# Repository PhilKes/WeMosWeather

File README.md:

# WeMosWeather  
## 3D Printed Solar powered Weather station
## Station

* 3D Printed Case (PLA) (created with [Autodesk 123Design](https://autodesk-123d-design.en.lo4d.com/windows))
* [BME 280](https://de.aliexpress.com/item/32801639254.html?src=google&src=google&albch=shopping&acnt=494-037-6276&isdl=y&slnk=&plac=&mtctp=&albbt=Gploogle_7_shopping&aff_atform=google&aff_short_key=UneMJZVf&&albagn=888888&albcp=1705854617&albag=67310370915&trgt=743612850714&crea=de32801639254&netw=u&device=c&albpg=743612850714&albpd=de32801639254&gclid=EAIaIQobChMIqMSEpN7e6gIVkLt3Ch35YAZTEAQYASABEgLxBfD_BwE&gclsrc=aw.ds)
* [WeMos D1 Mini](https://docs.wemos.cc/en/latest/d1/d1_mini.html)
* Light Sensor
* 3.7V Lithium Ion Battery 18650

## Sketch
* Arduino .ino Sketch for WeMos D1 mini/ESP ([sketch_solar_weather_thingspeak](/sketch_solar_weather_thingspeak))
* Reads and Posts Sensor Data to Thingspeak in interval (every 5 min)
* Uses ESP.deepSleep to save most Power

#### Dependencies
* [ESPAsyncWebServer](https://github.com/me-no-dev/ESPAsyncWebServer)
* [ESPAsyncTCP](https://github.com/me-no-dev/ESPAsyncTCP)
* [ESP8266-FS-Uploader](https://randomnerdtutorials.com/install-esp8266-filesystem-uploader-arduino-ide/)

## Android App

* Fetches Data from Thingspeak Server
* Displays Data on UI Dashboard
* Shows History of all collected Data

### TODOs
* Home Screen Widget
* Weather Prediction based on Pressure values

#### Dependencies
* [HelloCharts](https://github.com/lecho/hellocharts-android)
* [Material Design](https://material.io/components)

## Thingspeak Api
* Create a free Account on Thingspeak
* Add a private Channel with Field 1 (Temperature), Field 2 (Pressure), Field 3 (Humidity)
* To allow the Android App and WeMos Sketch to post/read Data to/from Thingspeak add the following files:

/sketch/solar_weather_thingspeak/**api.h**:

    const char* api_key = <YOUR_THINGSPEAK_CHANNEL_API_KEY>;
    char ssid[] = <YOUR_WIFI>;
    char pass[] = <WIFI_PASSWORD>;

/android/app/src/main/res/values/**api.xml**:

    <?xml version="1.0" encoding="utf-8"?>
    <resources>
        <item name="THINGSPEAK_READ_KEY" type="string"><YOUR_THINGSPEAK_CHANNEL_READ_KEY></item>
        <item name="THINGSPEAK_CHANNEL" type="string"><YOUR_THINGSPEAK_CHANNEL_ID></item>
    </resources>

## Web Page
* Alternative [sketch_solar_weather_webasync](/sketch_solar_weather_webasync)
* Basic static HTML Page to View Station Data directly from the WeMos
* Bootstrap Design
* URL: http://<WEMOS_IP_ADRESS>

### Sources
* [Thingspeak](https://thingspeak.com/)
* [Instructables](https://www.instructables.com/id/Solar-Powered-WiFi-Weather-Station/)
* [Esp8266 Bootstrap Example](https://diyprojects.io/bootstrap-create-beautiful-web-interface-projects-esp8266/#.XxcEGJ4zaUk)

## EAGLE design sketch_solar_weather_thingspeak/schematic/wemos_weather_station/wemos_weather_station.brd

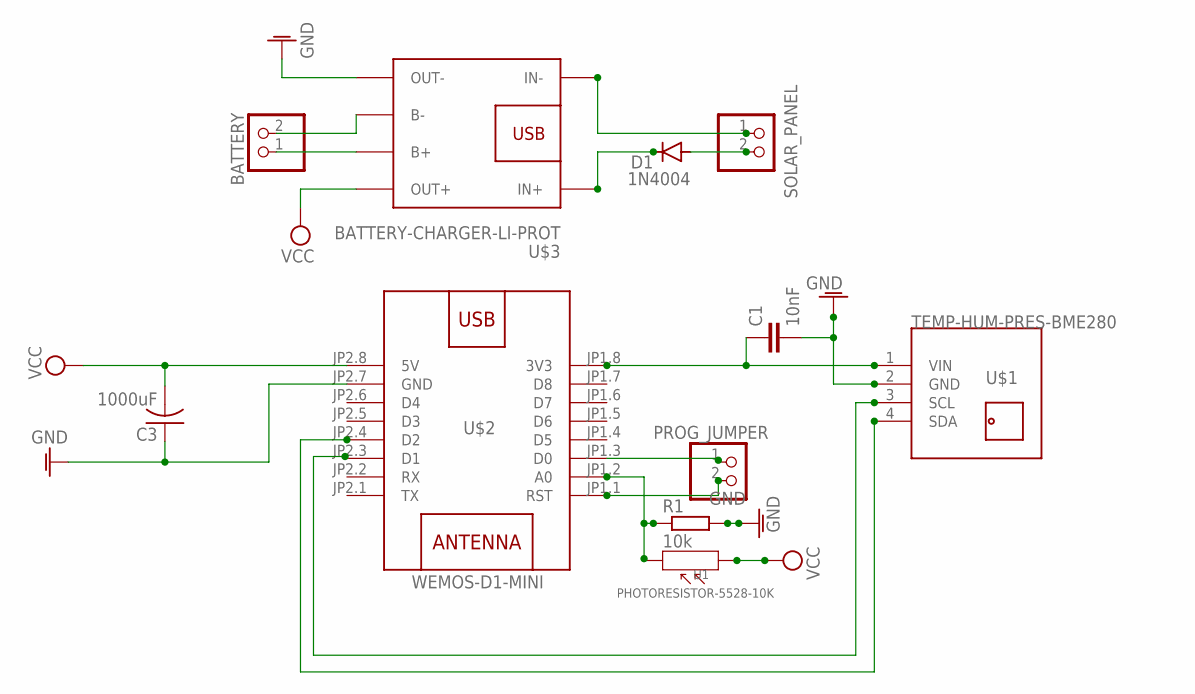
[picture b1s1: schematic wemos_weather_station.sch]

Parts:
BATTERY: PINHD-1X2; 1X02
C1: 10nF; C025-025X050
C3: 1000uF; C050-024X044
D1: 1N4004; DO41-10
PROG_JUMPER: PINHD-1X2; 1X02
R1: 10k; 0204/7
SOLAR_PANEL: PINHD-1X2; 1X02
U1: PHOTORESISTOR-5528-10K; SNR2-3.0
U$1: TEMP-HUM-PRES-BME280
U$2: WEMOS-D1-MINI
U$3: BATTERY-CHARGER-LI-PROT

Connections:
GND: C1.2, C3.1, R1.2, U$1.2 (GND), U$2.JP2.7 (GND), U$3.OUT-
unnamed: SOLAR_PANEL.1, U$3.IN-
unnamed: D1.C, U$3.IN+
unnamed: BATTERY.1, U$3.B+
unnamed: BATTERY.2, U$3.B-
unnamed: D1.A, SOLAR_PANEL.2
unnamed: PROG_JUMPER.1, U$2.JP1.3 (D0)
unnamed: C1.1, U$1.1 (VIN), U$2.JP1.8 (3V3)
unnamed: U$1.4 (SDA), U$2.JP2.4 (D2)
unnamed: U$1.3 (SCL), U$2.JP2.3 (D1)
unnamed: PROG_JUMPER.2, U$2.JP1.1 (RST)
unnamed: R1.1, U1.2, U$2.JP1.2 (A0)
VCC: C3.2, U1.1, U$2.JP2.8 (5V), U$3.OUT+

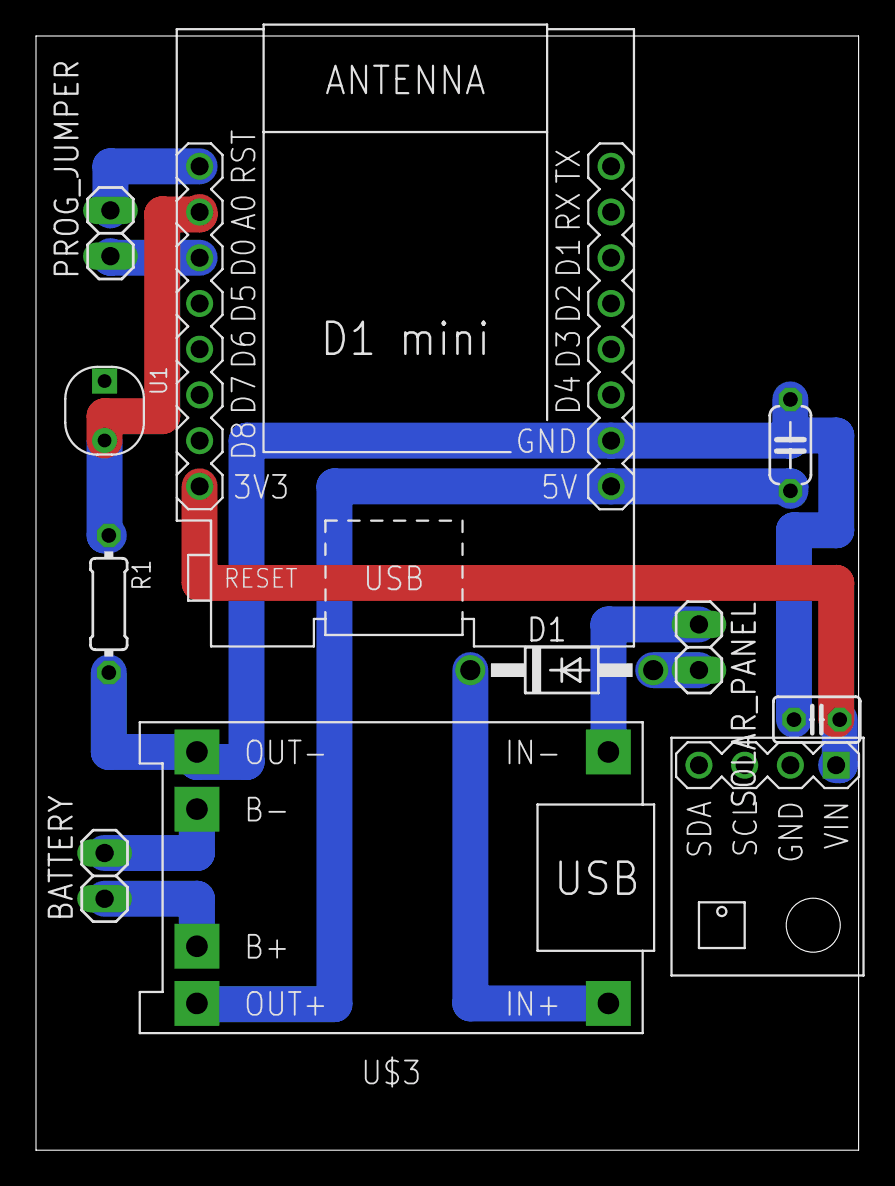
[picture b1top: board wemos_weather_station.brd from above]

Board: 2 copper layers, 45.7 x 61.9 mm, 11 parts (0 on the bottom side), 13 nets.

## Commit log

2020-07-21 initial web sketch with bootstrap
2020-07-21 webpage.html + .gitignore added
2020-07-23 Charts.js + NTPClient added
2020-07-23 AsyncWebServer with HTTP Endpoints + SPIFF Data Upload
2020-07-23 Placeholder in index.html + continous updates + Buffer for 24h, update every 5 min
2020-07-24 Android app added
2020-07-25 feat: Android App with Temperature + Humidity display + HTTP Updates
2020-07-25 assets: Logo added
2020-07-25 README.md updated
2020-07-25 assets/logo.png added
2020-07-25 feat: Android UI Dashboard mockup
2020-07-25 feat: Thingspeak support sketch added
2020-07-25 feat: MQTT Subscribe Thingspeak Channel
2020-07-25 refactor: styling Colors
2020-07-26 feat: Wemos deepSleep + Android: load initial Thingspeak Channel data
2020-07-26 feat: DataSet auto update on Thingspeak update + Last 7 Days Charts
2020-07-27 feat: Humidity included in LineChart + Coloring Test Sketch added
2020-07-28 feat: Generate DataSet + Autoupdate fix
2020-07-28 feat: Auto Select newest DataEntry + Show Date & Time of selected DataEntry
2020-08-01 3D Model files added
2020-08-01 3D Model fixes
2020-08-02 Regenerated Thingspeak Api Keys + hide api.h + api.xml files
2020-08-02 Eagle schematic added
2020-08-05 Schematic updated
2020-08-11 Humidity minor scale fixes
2020-08-11 feat: Slider Animation on Update
2020-08-14 added <=Android 6.0 compatibility
2020-08-19 History Activity added showing all data of past 7 Days
2020-08-19 fix: optimize ThingSpeak requests for History Data
2020-08-19 minor fixes
2020-08-28 Android: fixed invalid DataEntry deserialze + force Portrait Mode
2020-09-13 Android ScreenOrientation fixed to sensorPortrait
2020-09-13 Added Weather Icon for Prediction + Styling
2020-09-18 Weather Prediction based on Pressure Differences added
2020-09-19 display Weather Prediction of any selected Entry
2020-09-26 Weather prediction also based on absolute pressure values
2020-10-14 fix: if HourData empty show no Prediction
2020-11-01 fix: Rain Prediction based on Humidity

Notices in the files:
parts and their libraries:
diy-modules: Released under the Creative Commons Attribution 4.0 International License: http://creativecommons.org/licenses/by/4.0
